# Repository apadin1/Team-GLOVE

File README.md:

# Team-GLOVE
## EECS 473 Final Project

This project was created as part of a Major Design Experience (MDE) by five senior Computer Engineering students at the University of Michigan. The goal of the project was to create a pair of gloves that could behave as controllers for any PC video game using the standard HID protocol. The gloves collected data from flex sensors in the fingers, capacitive touch sensors in the fingertips, and an IMU mounted on the back of the hand, and transmitted this data wirelessly over bluetooth to a receiver board which translated the data into stardard keyboard and mouse commands. To read more about the results of this project, you can see our [final report](Team%20GLOVE%20Final%20Report.pdf) and [project poster](Team%20GLOVE%20Poster.pptx.pdf) which are included in this repository.

We have decided to make this repository public in the hopes that others could expand upon our work. Our goal is to make video games more fun, intuitive, and immersive, and we hope that you can help.

Sincerely,

Team GLOVE

Nick Bertoldi, Ben Heckathorn, Ryan O'Keefe, Adrian Padin, Tim Schumacher

## Repository Organization
This repository is divided into several sections:
* ConfigApp - Contains code for a Windows app which was used to configure the inputs on the glove. It is mostly written in C#
* Hardware - This folder holdsthe eagle and gerber files for the PCB that was designed to run on the glove
* mbed-dongle-firmware - The code that ran on the reciever board (USB dongle) that did the translation and generated keyboard and mouse commands
* mbed-glove-firmware - The software running on the glove itself to collect sensor data and transmit to the receiver

## Compiling mbed-cli
This project was created using the mbed real-time operating system and libraries. It was specifically designed to run on the NRF51822 processor because of the built-in Bluetooth capabilities. 

To get started with the mbed environment, you can check out their website: www.developer.mbed.org

For instructions on how to setup the mbed-cli, see their documentation page: https://docs.mbed.com/docs/mbed-os-handbook/en/5.1/dev_tools/cli/

You will also need GCC ARM embedded compiler, version 4.9, which can be found here: https://launchpad.net/gcc-arm-embedded/4.9/4.9-2015-q3-update

For Linux users, we recommend installing to /usr/local/ (just `tar -xjvf` the download in that dir)

You will also need git, python, and several python dependencies, as described in the mbed-cli instructions

To setup the enviroment in our repo, go into the mbed-glove-firmware folder and type `mbed-deploy` to update the mbed-os lib

## Contributing
This software is licensed under the Apache 2.0 software license. If you would like to contribute, please submit a pull request and we can review your changes before we apply them. If you would like to use this project as a starting point for other projects, consider forking this repository using the Fork button above. Just be sure to cite this repository in your work!

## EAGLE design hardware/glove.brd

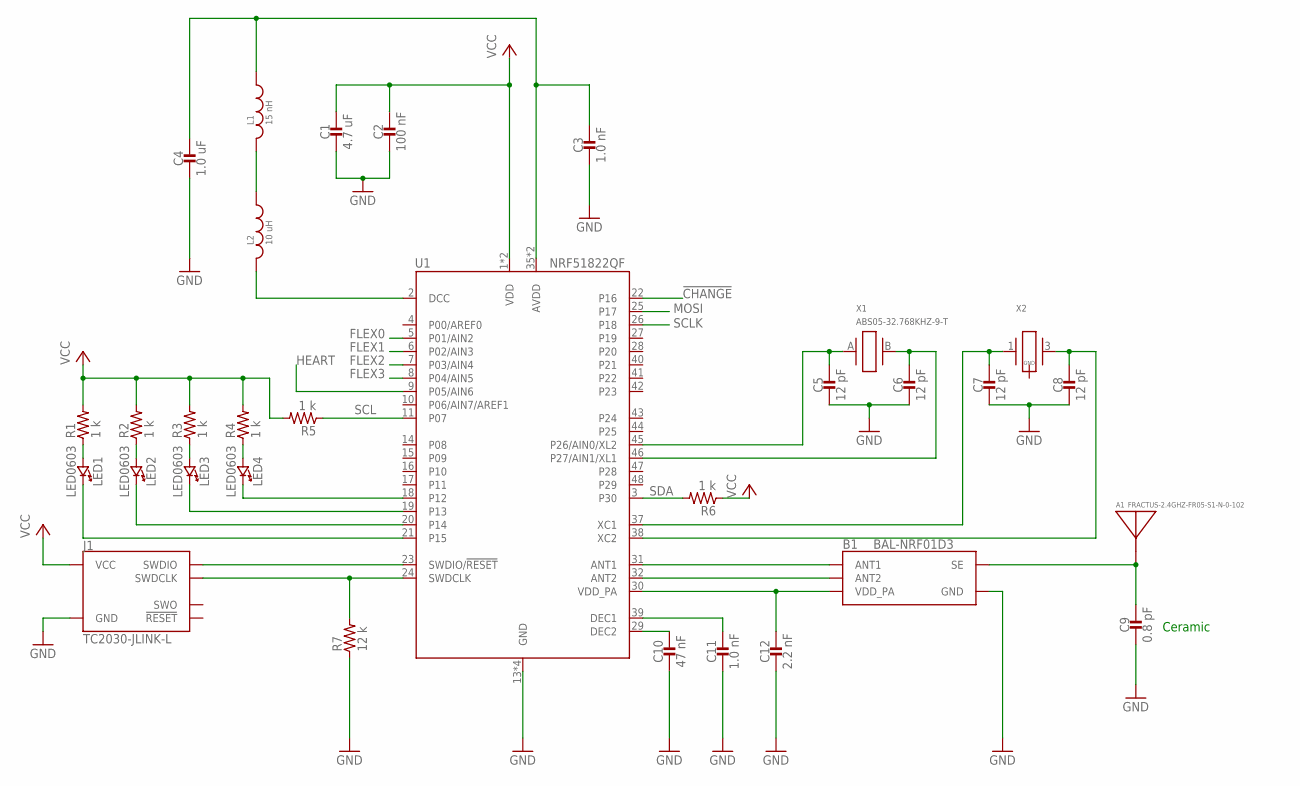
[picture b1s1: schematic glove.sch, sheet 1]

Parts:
A1: FRACTUS-2.4GHZ-FR05-S1-N-0-102; FRACTUS-ANTENNA-FR05-S1-N-0-102
B1: BAL-NRF01D3
C1: 4.7 uF; 0603_CAP
C2: 100 nF; 0402_CAP
C3, C11: 1.0 nF; 0402_CAP
C4: 1.0 uF; 0603_CAP
C5, C6, C7, C8: 12 pF; 0402_CAP
C9: 0.8 pF; 0402_CAP
C10: 47 nF; 0402_CAP
C12: 2.2 nF; 0402_CAP
J1: TC2030-JLINK-L; TC2030-IDC
L1: 15 nH; 0402_CAP
L2: 10 uH; 0603_CAP
LED1, LED2, LED3, LED4: LED0603; LED-0603
R1, R2, R3, R4, R5, R6: 1 k; 0603-RES
R7: 12 k; 0603-RES
U1: NRF51822QF; QFN-48-6MM
X1: ABS05-32.768KHZ-9-T; ABS05
X2: TXC-8Y

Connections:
!CHANGE: U1.22 (P16); also elsewhere on the board
FLEX0: U1.5 (P01/AIN2); also elsewhere on the board
FLEX1: U1.6 (P02/AIN3); also elsewhere on the board
FLEX2: U1.7 (P03/AIN4); also elsewhere on the board
FLEX3: U1.8 (P04/AIN5); also elsewhere on the board
GND: B1.GND, C1.2, C2.2, C3.2, C4.2, C5.2, C6.2, C7.2, C8.2, C9.2, C10.2, C11.2, C12.2, J1.5 (GND), R7.1, U1.13 (GND), U1.33 (GND), U1.34 (GND), U1.GND; also elsewhere on the board
HEART: U1.9 (P05/AIN6); also elsewhere on the board
MOSI: U1.25 (P17); also elsewhere on the board
unnamed: LED2.C (CATHODE), U1.20 (P14)
unnamed: LED2.A (ANODE), R2.1
unnamed: LED1.C (CATHODE), U1.21 (P15)
unnamed: LED1.A (ANODE), R1.1
unnamed: LED4.C (CATHODE), U1.18 (P12)
unnamed: LED4.A (ANODE), R4.1
unnamed: L2.2, U1.2 (DCC)
unnamed: L1.2, L2.1
unnamed: C3.1, C4.1, L1.1, U1.35 (AVDD), U1.36 (AVDD)
unnamed: J1.2 (SWDIO), U1.23 (SWDIO/!RESET)
unnamed: C8.1, U1.38 (XC2), X2.3 (2)
unnamed: B1.ANT1, U1.31 (ANT1)
unnamed: B1.ANT2, U1.32 (ANT2)
unnamed: B1.VCC (VDD_PA), C12.1, U1.30 (VDD_PA)
unnamed: A1.1, B1.SE, C9.1
unnamed: C10.1, U1.29 (DEC2)
unnamed: C11.1, U1.39 (DEC1)
unnamed: C5.1, U1.45 (P26/AIN0/XL2), X1.A (1)
unnamed: C6.1, U1.46 (P27/AIN1/XL1), X1.B (2)
unnamed: C7.1, U1.37 (XC1), X2.1
unnamed: J1.4 (SWDCLK), R7.2, U1.24 (SWDCLK)
unnamed: LED3.A (ANODE), R3.1
unnamed: LED3.C (CATHODE), U1.19 (P13)
SCL: R5.1, U1.11 (P07); also elsewhere on the board
SCLK: U1.26 (P18); also elsewhere on the board
SDA: R6.2, U1.3 (P30); also elsewhere on the board
VCC: C1.1, C2.1, J1.1 (VCC), R1.2, R2.2, R3.2, R4.2, R5.2, R6.1, U1.1 (VDD), U1.12 (VDD); also elsewhere on the board

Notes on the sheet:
Ceramic

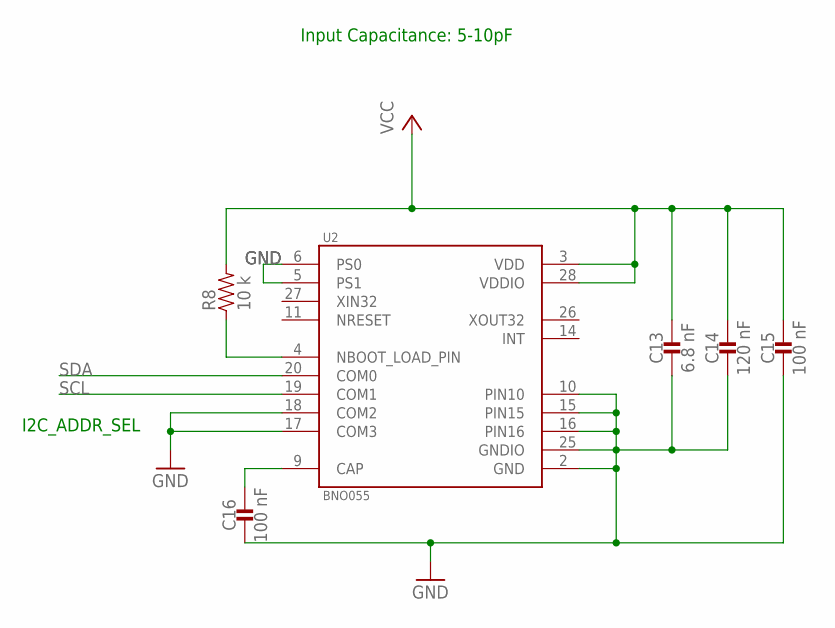
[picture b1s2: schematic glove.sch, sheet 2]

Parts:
C13: 6.8 nF; 0603_CAP
C14: 120 nF; 0603_CAP
C15, C16: 100 nF; 0603_CAP
R8: 10 k; 0603-RES
U2: BNO055; LGA28R50P4X10_380X520X100

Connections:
GND: C13.2, C14.2, C15.2, C16.2, U2.2 (GND), U2.5 (PS1), U2.6 (PS0), U2.10 (PIN10), U2.15 (PIN15), U2.16 (PIN16), U2.17 (COM3), U2.18 (COM2), U2.25 (GNDIO); also elsewhere on the board
unnamed: C16.1, U2.9 (CAP)
unnamed: R8.1, U2.4 (NBOOT_LOAD_PIN)
SCL: U2.19 (COM1); also elsewhere on the board
SDA: U2.20 (COM0); also elsewhere on the board
VCC: C13.1, C14.1, C15.1, R8.2, U2.3 (VDD), U2.28 (VDDIO); also elsewhere on the board

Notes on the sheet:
I2C_ADDR_SEL
Input Capacitance: 5-10pF

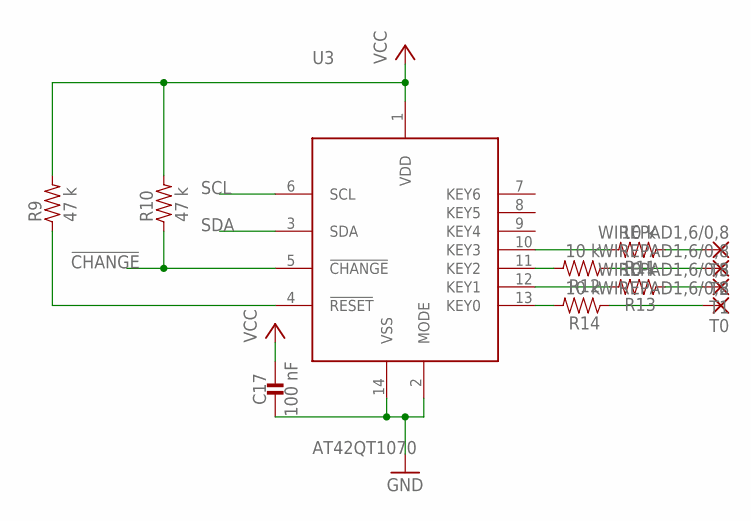
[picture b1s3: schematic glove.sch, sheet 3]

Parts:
C17: 100 nF; 0603_CAP
R9, R10: 47 k; 0603-RES
R11, R12, R13, R14: 10 k; 0603-RES
T0, T1, T2, T3: WIREPAD1,6/0,8; 1,6/0,8
U3: AT42QT1070; QT1070

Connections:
!CHANGE: R10.1, U3.5 (!CHANGE); also elsewhere on the board
GND: C17.2, U3.2 (MODE), U3.14 (VSS); also elsewhere on the board
unnamed: R11.2, U3.10 (KEY3)
unnamed: R11.1, T3.1
unnamed: R12.2, U3.11 (KEY2)
unnamed: R12.1, T2.1
unnamed: R13.2, U3.12 (KEY1)
unnamed: R13.1, T1.1
unnamed: R14.2, U3.13 (KEY0)
unnamed: R14.1, T0.1
unnamed: R9.1, U3.4 (!RESET)
SCL: U3.6 (SCL); also elsewhere on the board
SDA: U3.3 (SDA); also elsewhere on the board
VCC: C17.1, R9.2, R10.2, U3.1 (VDD); also elsewhere on the board

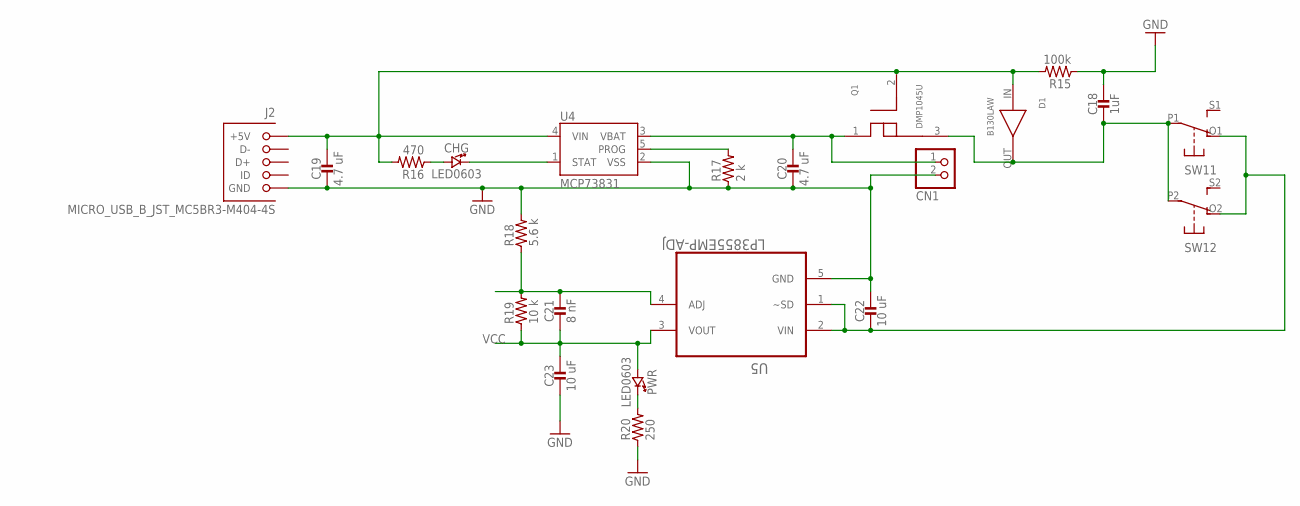
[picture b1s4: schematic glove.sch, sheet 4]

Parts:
C18: 1uF; 0603_CAP
C19, C20: 4.7 uF; 0603_CAP
C21: 8 nF; 0603_CAP
C22, C23: 10 uF; 0603_CAP
CHG: LED0603; LED-0603
CN1: JST_2PIN-SMT-RA; JST-PH-2-SMT-RA
D1: B130LAW; 2PIN
J2: MICRO_USB_B_JST_MC5BR3-M404-4S; USB_MICRO_B-JST-MC5BR3-M404-4S-TB
PWR: LED0603; LED-0603
Q1: DMP1045U; 3PIN
R15: 100k; 0603-RES
R16: 470; 0603-RES
R17: 2 k; 0603-RES
R18: 5.6 k; 0603-RES
R19: 10 k; 0603-RES
R20: 250; 0603-RES
SW1: DPDT-EG1390; EG1390
U4: MCP73831; SOT23-5
U5: LP3855EMP-ADJ; SOT150P696X180-5N

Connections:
GND: C18.1, C19.2, C20.2, C22.1, C23.2, CN1.2 (1), J2.5 (GND), R15.1, R17.1, R18.2, R20.1, U4.2 (VSS), U5.5 (GND); also elsewhere on the board
unnamed: C18.2, D1.OUT, Q1.3 (SOURCE), SW1.P1, SW1.P2
unnamed: CHG.A (ANODE), R16.1
unnamed: CHG.C (CATHODE), U4.1 (STAT)
unnamed: R17.2, U4.5 (PROG)
unnamed: C21.1, R18.1, R19.2, U5.4 (ADJ)
unnamed: PWR.C (CATHODE), R20.2
unnamed: C19.1, D1.IN, J2.1 (+5V), Q1.2 (GATE), R15.2, R16.2, U4.4 (VIN)
unnamed: C20.1, CN1.1 (2), Q1.1 (DRAIN), U4.3 (VBAT)
unnamed: C22.2, SW1.O1 (O), SW1.O2 (O), U5.1 (~SD), U5.2 (VIN)
VCC: C21.2, C23.1, PWR.A (ANODE), R19.1, U5.3 (VOUT); also elsewhere on the board

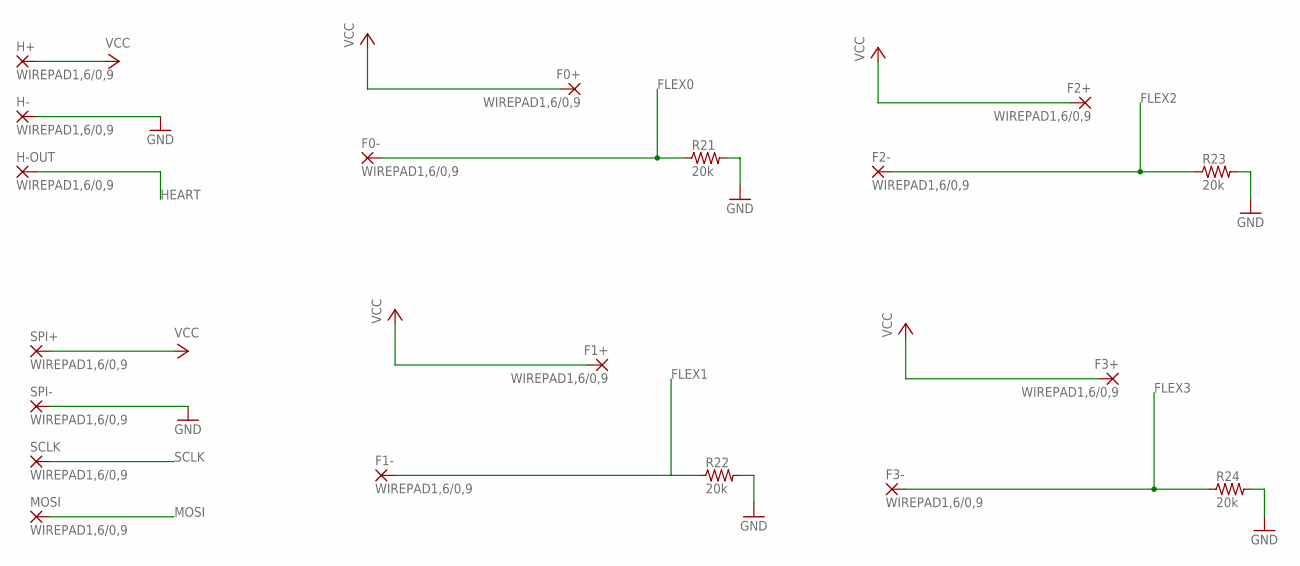
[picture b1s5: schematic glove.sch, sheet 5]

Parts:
F0+, F0-, F1+, F1-, F2+, F2-, F3+, F3-: WIREPAD1,6/0,9; 1,6/0,9
H+: WIREPAD1,6/0,9; 1,6/0,9
H-: WIREPAD1,6/0,9; 1,6/0,9
H-OUT: WIREPAD1,6/0,9; 1,6/0,9
MOSI: WIREPAD1,6/0,9; 1,6/0,9
R21, R22, R23, R24: 20k; 0603-RES
SCLK: WIREPAD1,6/0,9; 1,6/0,9
SPI+: WIREPAD1,6/0,9; 1,6/0,9
SPI-: WIREPAD1,6/0,9; 1,6/0,9

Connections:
FLEX0: F0-.1, R21.1; also elsewhere on the board
FLEX1: F1-.1, R22.1; also elsewhere on the board
FLEX2: F2-.1, R23.1; also elsewhere on the board
FLEX3: F3-.1, R24.1; also elsewhere on the board
GND: H-.1, R21.2, R22.2, R23.2, R24.2, SPI-.1; also elsewhere on the board
HEART: H-OUT.1; also elsewhere on the board
MOSI: MOSI.1; also elsewhere on the board
SCLK: SCLK.1; also elsewhere on the board
VCC: F0+.1, F1+.1, F2+.1, F3+.1, H+.1, SPI+.1; also elsewhere on the board

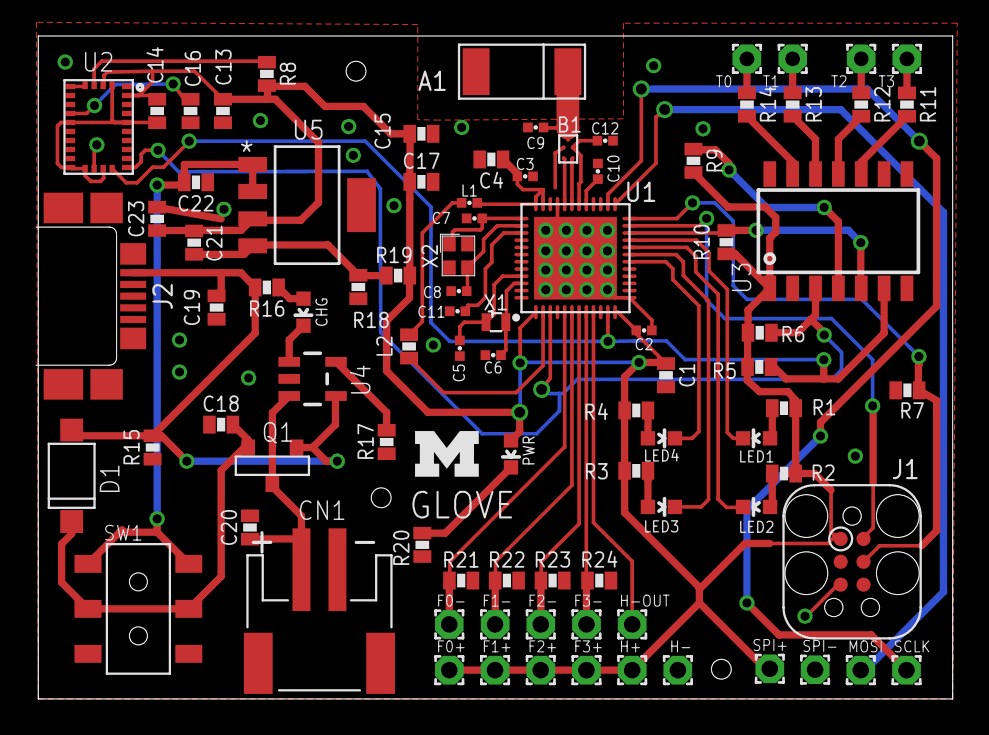
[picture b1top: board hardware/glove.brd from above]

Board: 2 copper layers, 50.9 x 36.8 mm, 90 parts (0 on the bottom side), 55 nets.

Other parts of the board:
U$1: UMICH_SOLID_100MIL

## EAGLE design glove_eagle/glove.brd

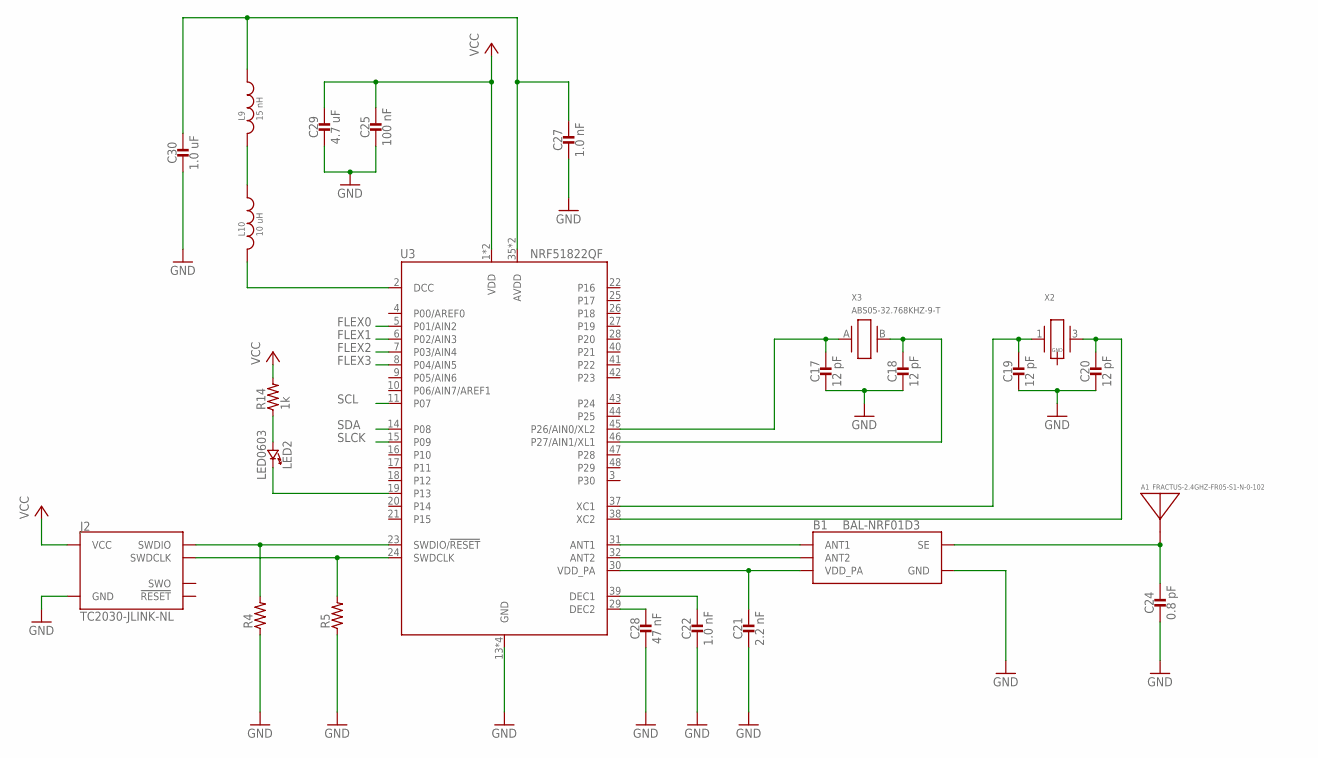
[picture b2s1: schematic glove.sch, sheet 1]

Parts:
A1: FRACTUS-2.4GHZ-FR05-S1-N-0-102; FRACTUS-ANTENNA-FR05-S1-N-0-102
B1: BAL-NRF01D3
C17, C18, C19, C20: 12 pF; 0402_CAP
C21: 2.2 nF; 0402_CAP
C22, C27: 1.0 nF; 0402_CAP
C24: 0.8 pF; 0402_CAP
C25: 100 nF; 0402_CAP
C28: 47 nF; 0402_CAP
C29: 4.7 uF; 0603_CAP
C30: 1.0 uF; 0603_CAP
J2: TC2030-JLINK-NL; TC2030-IDC-NL
L9: 15 nH; 0402_CAP
L10: 10 uH; 0603_CAP
LED2: LED0603; LED-0603
R4, R5: RESISTOR0603_RES; 0603-RES
R14: 1k; 0603-RES
U3: NRF51822QF; QFN-48-6MM
X2: TXC-8Y
X3: ABS05-32.768KHZ-9-T; ABS05

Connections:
FLEX0: U3.5 (P01/AIN2)
FLEX1: U3.6 (P02/AIN3)
FLEX2: U3.7 (P03/AIN4)
FLEX3: U3.8 (P04/AIN5)
GND: B1.GND, C17.2, C18.2, C19.2, C20.2, C21.2, C22.2, C24.2, C25.2, C27.2, C28.2, C29.2, C30.2, J2.5 (GND), R4.1, R5.1, U3.13 (GND), U3.33 (GND), U3.34 (GND), U3.GND; also elsewhere on the board
unnamed: LED2.C (CATHODE), U3.19 (P13)
unnamed: LED2.A (ANODE), R14.1
unnamed: L10.2, U3.2 (DCC)
unnamed: L9.2, L10.1
unnamed: C27.1, C30.1, L9.1, U3.35 (AVDD), U3.36 (AVDD)
unnamed: J2.2 (SWDIO), R4.2, U3.23 (SWDIO/!RESET)
unnamed: C20.1, U3.38 (XC2), X2.3 (2)
unnamed: B1.ANT1, U3.31 (ANT1)
unnamed: B1.ANT2, U3.32 (ANT2)
unnamed: B1.VCC (VDD_PA), C21.1, U3.30 (VDD_PA)
unnamed: A1.1, B1.SE, C24.1
unnamed: C28.1, U3.29 (DEC2)
unnamed: C22.1, U3.39 (DEC1)
unnamed: C17.1, U3.45 (P26/AIN0/XL2), X3.A (1)
unnamed: C18.1, U3.46 (P27/AIN1/XL1), X3.B (2)
unnamed: C19.1, U3.37 (XC1), X2.1
unnamed: J2.4 (SWDCLK), R5.2, U3.24 (SWDCLK)
SCL: U3.11 (P07); also elsewhere on the board
SDA: U3.14 (P08); also elsewhere on the board
SLCK: U3.15 (P09)
VCC: C25.1, C29.1, J2.1 (VCC), R14.2, U3.1 (VDD), U3.12 (VDD); also elsewhere on the board

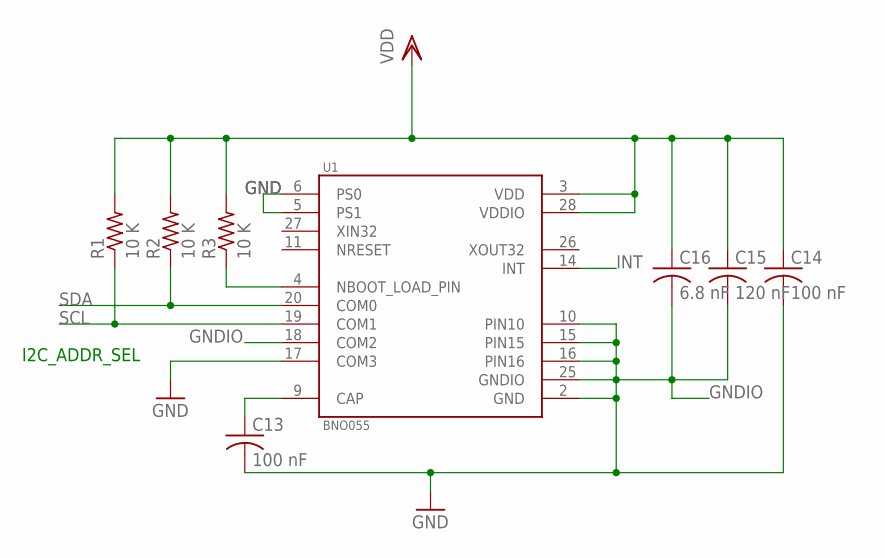
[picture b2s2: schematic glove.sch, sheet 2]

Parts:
C13, C14: 100 nF; C0603
C15: 120 nF; C0603
C16: 6.8 nF; C0603
R1, R2, R3: 10 K; R0603
U1: BNO055; LGA28R50P4X10_380X520X100

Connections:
GND: U1.5 (PS1), U1.6 (PS0), U1.17 (COM3); also elsewhere on the board
GNDIO: C13.2, C14.2, C15.2, C16.2, U1.2 (GND), U1.10 (PIN10), U1.15 (PIN15), U1.16 (PIN16), U1.18 (COM2), U1.25 (GNDIO)
INT: U1.14 (INT)
unnamed: C13.1, U1.9 (CAP)
unnamed: R3.1, U1.4 (NBOOT_LOAD_PIN)
SCL: R1.1, U1.19 (COM1); also elsewhere on the board
SDA: R2.1, U1.20 (COM0); also elsewhere on the board
VDD: C14.1, C15.1, C16.1, R1.2, R2.2, R3.2, U1.3 (VDD), U1.28 (VDDIO)

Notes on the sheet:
I2C_ADDR_SEL

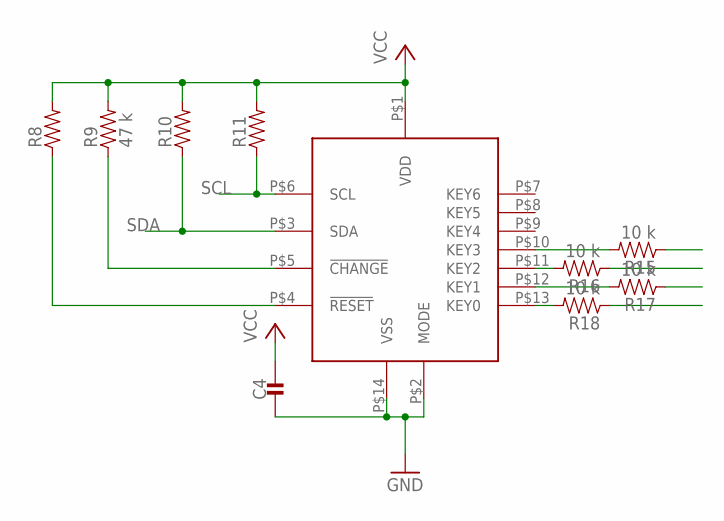
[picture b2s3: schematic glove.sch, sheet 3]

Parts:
C4: CAPACITOR0603_CAP; 0603_CAP
R8, R10, R11: RESISTOR0603_RES; 0603-RES
R9: 47 k; 0603-RES
R15, R16, R17, R18: 10 k; 0603-RES
U$1: COMMS; QT1070

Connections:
GND: C4.2, U$1.P$2 (MODE), U$1.P$14 (VSS); also elsewhere on the board
unnamed: R9.1, U$1.P$5 (!CHANGE)
unnamed: R15.2, U$1.P$10 (KEY3)
unnamed: R16.2, U$1.P$11 (KEY2)
unnamed: R17.2, U$1.P$12 (KEY1)
unnamed: R18.2, U$1.P$13 (KEY0)
unnamed: R8.1, U$1.P$4 (!RESET)
SCL: R11.1, U$1.P$6 (SCL); also elsewhere on the board
SDA: R10.1, U$1.P$3 (SDA); also elsewhere on the board
VCC: C4.1, R8.2, R9.2, R10.2, R11.2, U$1.P$1 (VDD); also elsewhere on the board

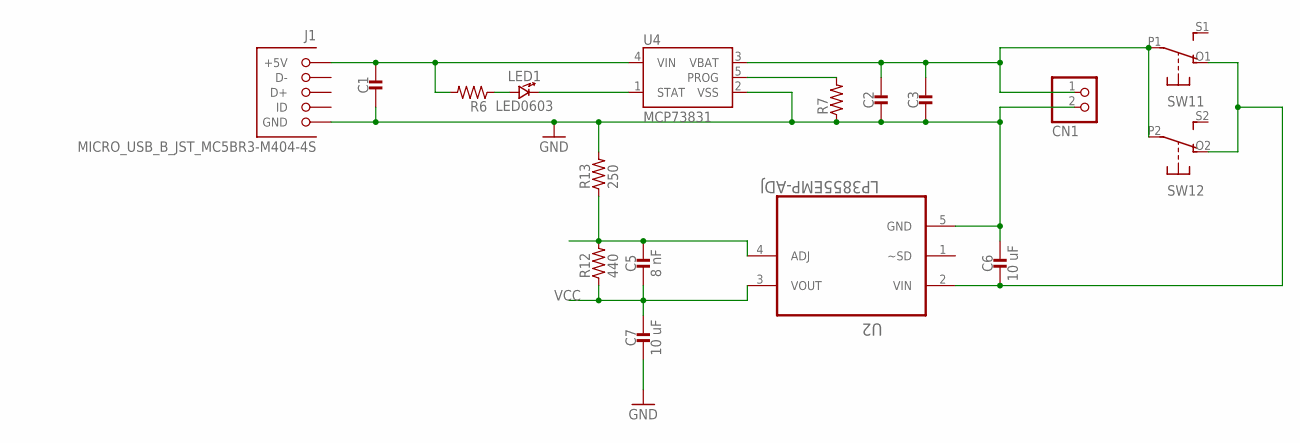
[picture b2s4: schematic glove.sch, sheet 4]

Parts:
C1, C2, C3: CAPACITOR0603_CAP; 0603_CAP
C5: 8 nF; 0603_CAP
C6, C7: 10 uF; 0603_CAP
CN1: JST_2PIN-SMT-RA; JST-PH-2-SMT-RA
J1: MICRO_USB_B_JST_MC5BR3-M404-4S; USB_MICRO_B-JST-MC5BR3-M404-4S-TB
LED1: LED0603; LED-0603
R6, R7: RESISTOR0603_RES; 0603-RES
R12: 440; 0603-RES
R13: 250; 0603-RES
SW1: DPDT-EG1390; EG1390
U2: LP3855EMP-ADJ; SOT150P696X180-5N
U4: MCP73831; SOT23-5

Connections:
GND: C1.2, C2.2, C3.2, C6.1, C7.2, CN1.2 (1), J1.5 (GND), R7.1, R13.2, U2.5 (GND), U4.2 (VSS); also elsewhere on the board
unnamed: C2.1, C3.1, CN1.1 (2), SW1.P1, SW1.P2, U4.3 (VBAT)
unnamed: LED1.A (ANODE), R6.1
unnamed: LED1.C (CATHODE), U4.1 (STAT)
unnamed: R7.2, U4.5 (PROG)
unnamed: C6.2, SW1.O1 (O), SW1.O2 (O), U2.2 (VIN)
unnamed: C5.1, R12.2, R13.1, U2.4 (ADJ)
unnamed: C1.1, J1.1 (+5V), R6.2, U4.4 (VIN)
VCC: C5.2, C7.1, R12.1, U2.3 (VOUT); also elsewhere on the board

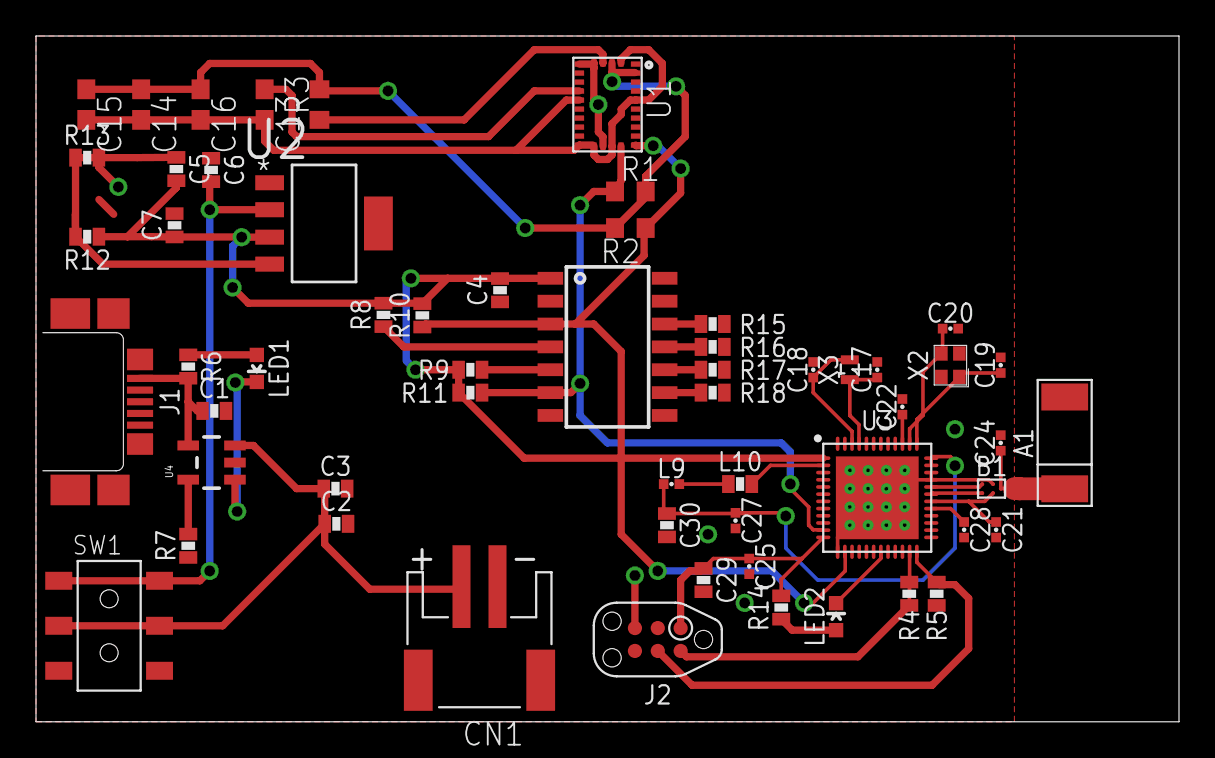
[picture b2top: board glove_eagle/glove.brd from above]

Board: 2 copper layers, 63.5 x 38.1 mm, 58 parts (0 on the bottom side), 38 nets.

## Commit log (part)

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2016-11-04 turns out they're not quite done...damn
2016-11-05 Most final board issues fixed - one or two to go
2016-11-06 Using the right mounting point
2016-11-06 Likely Ready to Order
2016-11-06 Optional compile for two differing prototype gloves
2016-11-06 DONT lock around printf with rtos tasks...
2016-11-07 General outline for gestureCheck() functionality, added additional TODOs
2016-11-07 Added more description to translator. Modified constuctor and enum
2016-11-07 Removed old headers
2016-11-07 Updated header files for new interface
2016-11-07 Remove compile -D INCL_TOUCH
2016-11-07 Revised collector for translator, integrated collector read functions into updateGesture()
2016-11-08 Moved collector functionality to translator
2016-11-08 Removed un-compilable files
2016-11-08 First analog button class
2016-11-08 Added threshold calculation arithmatic
2016-11-08 Finished fleshing out the analog button
2016-11-08 Pass transition band percent thru
2016-11-08 Initial commit for updated inputToHID
2016-11-08 Basic code and pseudocode for updated translator class
2016-11-08 beginning to build on top of analog button
2016-11-08 Modified some analog_button functionality
    Realised that since any one sensor only represents one portion of a mouse, not whole mouse, the old
    design of mouseData did not make much sense. Redesign to new scheme that mirrors keyboardData
2016-11-08 Translator, additional comments, initial integration of analog_button class to gestureCheck() periodic function, initial proposal for updateGestureMap() functionality
2016-11-08 Minor changes for updated analog_button class
2016-11-08 Added Ryan's Dot Star proof of concept
2016-11-08 More with the lights, interface works
2016-11-08 A bunch of demo code for the glove prototype
2016-11-08 Changed the name
2016-11-08 Adds cpp file for the DotStarLEDs class
2016-11-08 Working!
2016-11-08 Adds option to set all leds in strand
2016-11-08 Placed declaration in the header for maths fns
2016-11-09 Tweaks to the imu->lights code, imu mount point
2016-11-09 Added simple debug out pin
2016-11-09 Added the BLE API lib file
2016-11-09 analog_button comming along nicely. Should be done soon.
2016-11-09 analog_button v1 done.
    need to read through, but I think it should work.
2016-11-09 initial integration between analog_button and translator
2016-11-10 translator absorbed collector, added initial code for translator constructor
2016-11-10 Updated constructor for new updated analog_button
2016-11-10 Fix compile error on callback params
2016-11-10 Get all the BLE/old main working together
2016-11-11 digital functionality should be working. Lets work on compilng now
2016-11-11 Translator: switched vector implementation to array
2016-11-11 jdbciobldajcnaidbhlvcadncialn dsc
2016-11-11 lol it compiles now yay
2016-11-11 New LED status thing with all 3 sensors
2016-11-11 it compiles...
2016-11-11 CHanged th4e lights
2016-11-13 fixed update_value syntax in analog_button
2016-11-14 Updates for new HID api. Potential fixes for main. Working spacebar demo for flexsensor1 in main
2016-11-14 added wasd function to keyboard mous demo. It works with touch sensors!
2016-11-15 Adjusted the blink() test function
2016-11-15 Removed mutex, rtos timer from IMU
2016-11-15 Removes mutex, rtos timer from flex sensors
2016-11-15 Removes mutex, debug out pin from touch sensors
2016-11-15 Moved all the sensor-only tests into own file
2016-11-15 Added extern function definitions
2016-11-15 Adjusted translator and main for new timing functionality
2016-11-15 Formatting in analog_button
2016-11-15 Formatting on translator
2016-11-17 Fixed connection callbacks
2016-11-17 redoing analog_button stuff yay...
2016-11-17 Added a cleaned up version of the USB joystick files
2016-11-17 new names yay
2016-11-17 working on stuff
2016-11-17 Use sensor tests
2016-11-17 Sorting out ble_hid
2016-11-17 Added updated touchToHid class
2016-11-17 Dynamic interrupt-in usage in touch sensor
2016-11-17 i am having so much fun
2016-11-17 Made keyboard_mouse_demo an extern != main Please enter the commit message for your changes. Lines starting
2016-11-17 updateAndWrite -> updateAndWriteSensors
2016-11-17 slowly getting flex to work
2016-11-17 Make main use the updateAndWrite calls
2016-11-17 Tweak the sensors to lights
2016-11-17 flex sensor for analog_button is completed, not tested
2016-11-17 translator updates for new analog_button class
2016-11-17 Working on the thing
2016-11-17 Working on timeout strategy for touch sensor
2016-11-18 Can kill task, now need to make sure it runs
2016-11-18 More things
2016-11-18 Building the infrastrucure into TouchSensor as much as possible
2016-11-18 Still works at faster speeds
2016-11-18 moved old analog class. Soon to be deleted (huzzah!)
2016-11-18 almost compiles v3
2016-11-18 Updates for new analog_button
2016-11-18 Fix connection callbacks
2016-11-18 Demo with flex sensor mapped to 'a'
2016-11-18 Encapsulated Thread* stuff in TouchSensor
2016-11-18 try this @Ben
2016-11-18 Removed pin outs
2016-11-18 Here ya go Ryan
2016-11-18 First pass ar BLE joystick service
2016-11-18 Added example files for Tim use
2016-11-18 More fleshing out on the joystick service
2016-11-20 Remove the update() function
2016-11-20 tweaking the joystick service api
2016-11-20 More work on the callbacks for testing
2016-11-20 my version of joystick_test
2016-11-20 Add callbacks and explicit "send" ble calls
2016-11-20 Using a new report descriptor for joystick
2016-11-21 hangs when bluetooth added. about to merge master
2016-11-21 flex sensor works as keyboard AND MOUSE bitches!
2016-11-21 all works, except yaw
2016-11-21 Working on the calibration mode
2016-11-22 Added back the button callbacks
2016-11-22 Restore joystick service
2016-11-22 send() returns BLE_STACK_BUSY error...
2016-11-28 Threaded touch sensor thing
2016-11-28 Scanning working
2016-11-29 Simplified security init
2016-11-29 Move to collector
2016-11-29 Restructured dongle-firmware folder
2016-11-29 Updates to translator for multiple gloves
2016-11-29 Translator updates for config
2016-11-29 General changes to main.cpp, additional changes to translator
2016-11-29 Added BLE advert header
2016-11-29 Renamed
2016-11-29 Collector now using the AdvertBLE
2016-11-29 Trying to get the collector with advertisements compiling
2016-11-29 Removed old config app
2016-11-29 New cpp for glove_sensors
2016-11-29 All the collector stuff
2016-11-30 Adds comparison before changin ble ad
2016-11-30 Working with debug pins...
2016-11-30 Working again, not really sure what I ended up changing
2016-12-01 Add scanner class
2016-12-01 Initial configuration updates to translator and analog_button
2016-12-01 Fixed main
2016-12-01 Fixed dependencies to get code to compile
2016-12-01 c sharp uart tests
2016-12-01 Fixed compile script in dongle-firmware
2016-12-01 fixed references issues in glove-firmware
2016-12-01 Changed indexing in translator config function for serial communication
2016-12-01 Using the pins on the PCB
2016-12-01 Commented out right glove translator code for testing
2016-12-01 Initial integration of translator object into scanner object
2016-12-01 Fixes to main to compile code
2016-12-01 Working advertisement
2016-12-01 Integrated rtos functionality into scanner class
2016-12-01 Advertising real glove data!
2016-12-01 Reorder the glove_data_compressed
2016-12-01 Added serial interrupt function
2016-12-01 added scanner object to serial_init
2016-12-01 Fixing compiler issues
2016-12-01 Adds crc function
2016-12-01 Compile fixes
2016-12-01 Added adjacent key suppression
2016-12-01 touch to lights code in sensor_tests
2016-12-01 all in same key group
2016-12-02 fixes for compilation
2016-12-02 imu pcb test
2016-12-02 start scan now runs continuously
2016-12-02 complete middle click functionality
2016-12-02 Timing adjestments for advertisements
2016-12-02 config test edits
2016-12-02 Fixes to scanning and serial receiving
2016-12-02 Working on things, tuning the advertising interval
2016-12-02 Cleaned up the ble_advert code now that it works
2016-12-02 Cleans up collector, AdvertBLE
2016-12-03 Trying to fix things...:
2016-12-03 Fix to hid stuff, separating ble out
2016-12-03 some changes to get master compiling
2016-12-04 Fixing bluetooth scanning
2016-12-04 Expanded the DotStar API
2016-12-04 small changes in debugging
2016-12-04 No cpp 11 :'(
2016-12-04 removed mbed from repo
2016-12-04 Small compile typos
2016-12-05 Working on button lights
2016-12-05 Testing
2016-12-05 Removes the mbed-os which shouldn't be included
2016-12-05 Cleans up the touch sensor; final lights
2016-12-05 Use Flex instead
2016-12-05 adjustments for translator per glove
2016-12-05 Cleaned up things
2016-12-05 New file with scanning mode
2016-12-05 waitForFuckingEvent may just be our BLE pancea
2016-12-05 Scan for the actual glove packets
2016-12-05 full touch translate functionality
2016-12-05 Full translator logic for ALL flex and touch sensors, IMU on the way
2016-12-06 fully functional translator, imu analog values still need to be tested
2016-12-06 Needs to measure linear accel I guess
2016-12-06 Output changes; imu still flatlining
2016-12-06 Using bitwise compression on the flex vals
2016-12-06 Adds working, tested version of glove data (de)compress
2016-12-06 Moved crc for reals now
2016-12-07 Refactored the light pattern to be data-driven
2016-12-07 Adds in touch notification
2016-12-07 Adding more indications
2016-12-07 Adds new glove data and scanner code
2016-12-07 imu logic needs fixing, config app is functional
2016-12-07 testing scanning
2016-12-07 It was complaining...
2016-12-07 trying this again
2016-12-07 Testing with two gloves
2016-12-07 changed glove ID to left:
2016-12-07 Two gloves not yet working...
2016-12-07 Add back in touch sensor lights
2016-12-07 Using touch-to-lights
2016-12-07 Using threads for the touch in the unit test
2016-12-07 other debug changes blah blah blah
2016-12-07 22.5 hours to go...
2016-12-07 imu seems to work too..
2016-12-07 Moved the reallo long duplicated translator code into functions
2016-12-07 Whitespace cleanup
2016-12-07 set up to respond to scans
2016-12-07 Change advert ID
2016-12-07 readded the print stuff in main (why were they even commented out?)
2016-12-07 Chang order of operations in collector
2016-12-07 added back led in collector
2016-12-07 Adjusted color patterns
2016-12-07 Added caching to the leds to remove quiver
2016-12-07 Left glove, red
2016-12-07 Names are hard
2016-12-07 Setup the right glove
2016-12-07 Added calibration for touch
2016-12-07 changing some stuffs around
2016-12-07 Color tweaks and adds calibration to touch
2016-12-07 DIRECTED didn't work, did not show up at all
2016-12-07 Using refs instead of pointers to classes
2016-12-07 making changes to have 2 gloves at the same time
2016-12-07 Fix packet len; checksum ignore
2016-12-07 Change left glove pattern
2016-12-08 Serial Int
2016-12-08 Adjusted the color palatte
2016-12-08 Changed the conditional compile thing
2016-12-08 testing more
2016-12-08 Swap pitch/roll; disable serialInt
2016-12-08 WOrking on the analog thing:wq gps
2016-12-08 Put raw glove data inside translator, among other things
2016-12-08 The mouse, is analog
2016-12-08 Portal is playable...... with one glove
2016-12-08 FIRST
2016-12-08 Chane up scanner
2016-12-08 New new in the new constructor
2016-12-08 Translator conversion complete
2016-12-08 Analog button and translator refactor; new out of memory
2016-12-08 Finished static memory of analog_button classes
2016-12-08 "Op new out of mem" error is gone
2016-12-08 Scanner working with both gloves
2016-12-08 We can now instantiate two translators (STACK FTW)
2016-12-08 We connected over bluetooth again!
2016-12-08 COmments:
2016-12-08 Mapped the valeus we need for potral on two gloves
2016-12-08 More config is done!
2016-12-08 Portal-specific colors now
2016-12-08 Using MAX_TOUCH_ON of 5s
2016-12-08 My Orange is orange you glad im a door hinge?
2016-12-08 CONFIG WORKS
2016-12-08 touch escape
2016-12-08 more updates
2016-12-08 more stuff
2016-12-08 final stuff
2016-12-10 Cleaning up top level, start licensing
2016-12-10 Added the license
2016-12-10 Removed code that lives on the dongle now
2016-12-10 Misc licensing and cleanup on the dongle
2016-12-10 Added LICENSE to config app
2016-12-12 Changed the name of the glove
2016-12-13 Tweaks to some more values while doing the demo video

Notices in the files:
parts and their libraries:
SparkFun-PowerIC: Licensing: CC v3.0 Share-Alike You are welcome to use this library for commercial purposes.
